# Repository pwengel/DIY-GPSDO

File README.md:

# DIY-GPSDO

Bearbeitet von Lukas

Paste the contents (2 files) of the symbols folder into [for me, this is Dokumente]/KiCad/8.0/symbols/
Symbols for the Pico: https://github.com/ncarandini/KiCad-RP-Pico

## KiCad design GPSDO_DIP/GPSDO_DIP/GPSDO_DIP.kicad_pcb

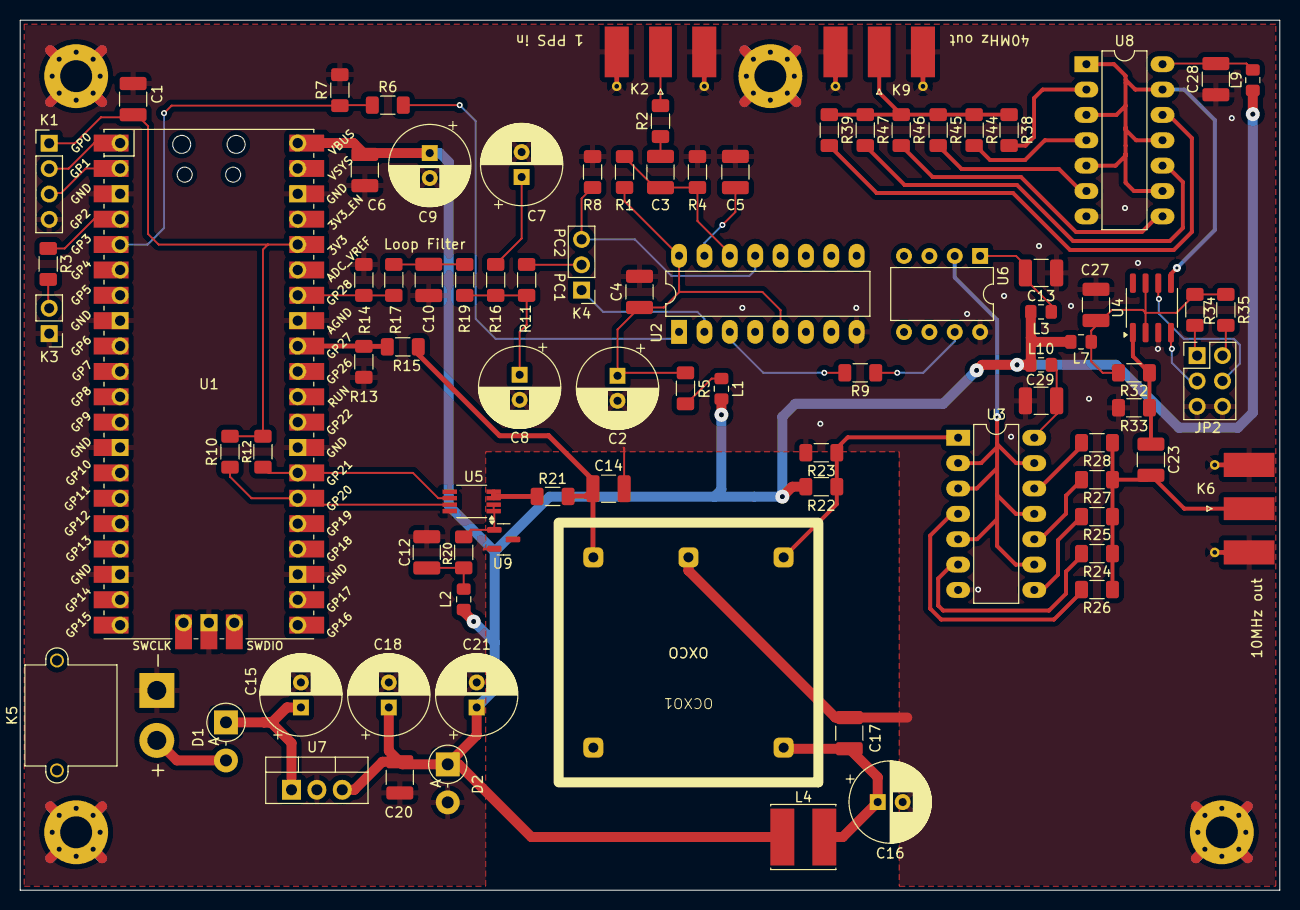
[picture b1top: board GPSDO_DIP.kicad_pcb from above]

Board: 2 copper layers, 126.1 x 87.1 mm, 87 parts (0 on the bottom side), 59 nets.

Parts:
C1, C4, C6, C12, C13, C14, C17, C20, C23, C27, C28, C29: 100n; C_1210_3225Metric_Pad1.33x2.70mm_HandSolder
C2, C7, C16, C21: 47µ; CP_Radial_D8.0mm_P2.50mm
C3, C10: 1µ; C_1210_3225Metric_Pad1.33x2.70mm_HandSolder
C5: 2.2n; C_1210_3225Metric_Pad1.33x2.70mm_HandSolder
C8: 22µ; CP_Radial_D8.0mm_P2.50mm
C9: 220µ; CP_Radial_D8.0mm_P2.50mm
C15, C18: 470µ; CP_Radial_D8.0mm_P2.50mm
D1: SS24; D_DO-15_P3.81mm_Vertical_AnodeUp
D2: D; D_DO-15_P3.81mm_Vertical_AnodeUp
JP2: Conn_02x03_Odd_Even; PinHeader_2x03_P2.54mm_Vertical
K1: Conn_01x04; PinHeader_1x04_P2.54mm_Vertical
K2, K6, K9: Conn_Coaxial; SMA_Molex_73251-1153_EdgeMount_Horizontal
K3: Conn_01x02; PinHeader_1x02_P2.54mm_Vertical
K4: Jumper_3_Open; PinHeader_1x03_P2.54mm_Vertical
K5: Conn_01x02; AMASS_XT30PW-M_1x02_P2.50mm_Horizontal
L1, L2: 100µ; L_0805_2012Metric_Pad1.15x1.40mm_HandSolder
L3, L7, L9, L10: 10µ; L_0805_2012Metric_Pad1.15x1.40mm_HandSolder
L4: 10µ; L_Cenker_CKCS6045
OCXO1: OSC5A2B02
R1, R4, R16, R22, R23: 22k; R_1206_3216Metric_Pad1.30x1.75mm_HandSolder
R2, R19, R24, R25, R26, R27, R28, R38, R39, R44, R45, R46, R47: 240; R_1206_3216Metric_Pad1.30x1.75mm_HandSolder
R3, R20: 1k; R_1206_3216Metric_Pad1.30x1.75mm_HandSolder
R5: 22; R_1206_3216Metric_Pad1.30x1.75mm_HandSolder
R6, R15, R17: 27k; R_1206_3216Metric_Pad1.30x1.75mm_HandSolder
R7, R13, R14: 47k; R_1206_3216Metric_Pad1.30x1.75mm_HandSolder
R8: 1M; R_1206_3216Metric_Pad1.30x1.75mm_HandSolder
R9, R21: 680; R_1206_3216Metric_Pad1.30x1.75mm_HandSolder
R10, R12: 10k; R_1206_3216Metric_Pad1.30x1.75mm_HandSolder
R11: 160k; R_1206_3216Metric_Pad1.30x1.75mm_HandSolder
R32, R33: 100k; R_1206_3216Metric_Pad1.30x1.75mm_HandSolder
R34, R35: 4.7k; R_1206_3216Metric_Pad1.30x1.75mm_HandSolder
U1: Pico; RPi_Pico_SMD_TH
U2: DIP-16_W7.62mm_LongPads
U3, U8: 74HC14; DIP-14_W7.62mm_LongPads
U4: U1; SOIC-8_3.9x4.9mm_P1.27mm
U5: DAC8571IDGK; VSSOP-8_3.0x3.0mm_P0.65mm
U6: PIC12F675-xP; DIP-8_W7.62mm
U7: LM7805_TO220; TO-220-3_Vertical
U9: LM4040DBZ-4.1; SOT-23

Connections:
/VCC: C6.1, C7.1, C18.1, C20.1, C21.1, D2.1 (K), L1.2, L2.2, L3.1, L4.1, L7.2, L9.1, L10.1, R22.1, U1.40 (VBUS), U7.3 (VO)
/V_LPF: C10.2, R17.2, R19.1
/V_OCXO: C14.1, OCXO1.3 (Vcont), R15.2, R21.1
GND: C1.2, C2.2, C4.2, C5.1, C6.2, C7.2, C8.2, C9.2, C10.1, C12.2, C13.1, C14.2, C15.2, C16.2, C17.2, C18.2, C20.2, C21.2, C27.2, C28.1, C29.1, D2.2 (A), JP2.5, JP2.6, K1.4, K2.2 (Ext), K3.1, K5.1, K6.2 (Ext), K9.2 (Ext), OCXO1.2 (GND), R4.2, R7.2, R8.2, R13.2, R14.2, R23.2, R33.2, U1.3 (GND), U1.8 (GND), U1.13 (GND), U1.18 (GND), U1.23 (GND), U1.28 (GND), U1.33 (AGND), U1.38 (GND), U1.42 (GND), U2.8 (GND), U3.7 (GND), U4.3 (GND), U5.5 (A0), U5.8 (GND), U6.8 (VSS), U7.2 (GND), U8.7 (GND), U9.2 (A)
unnamed: C3.1, R2.1
unnamed: C8.1, R11.2, R16.1, R19.2
unnamed: C9.1, R16.2
unnamed: C12.1, L2.1, R20.1
unnamed: D1.2 (A), K5.2
unnamed: C15.1, D1.1 (K), U7.1 (VI)
unnamed: JP2.1, R34.1
unnamed: JP2.2, R35.2
unnamed: JP2.3, U4.4 (S1)
unnamed: JP2.4, U4.6 (S0)
unnamed: C1.1, K1.1, R10.2, R12.2, U1.36 (3V3)
unnamed: K1.2, U1.1 (GPIO0)
unnamed: K1.3, U1.2 (GPIO1)
unnamed: K2.1 (In), R2.2
unnamed: K3.2, R3.2
unnamed: K4.1 (A), U2.2 (PC1_out)
unnamed: K4.3 (B), R8.1, U2.13 (PC2_out)
unnamed: K4.2 (C), R11.1
unnamed: C23.2, K6.1 (In), R24.1, R25.1, R26.1, R27.1, R28.1
unnamed: K9.1 (In), R38.1, R39.1, R44.1, R45.1, R46.1, R47.1
unnamed: L1.1, R5.1
unnamed: OCXO1.1 (10MHz), R22.2, R23.1, U3.1
unnamed: C16.1, C17.1, L4.2, OCXO1.5 (VCC)
unnamed: R24.2, U3.6
unnamed: R25.2, U3.8
unnamed: R26.2, U3.4
unnamed: R27.2, U3.10
unnamed: R28.2, U3.12
unnamed: R38.2, U8.2
unnamed: R39.2, U8.12
unnamed: R44.2, U8.4
unnamed: R45.2, U8.6
unnamed: R46.2, U8.8
unnamed: R47.2, U8.10
unnamed: R3.1, U1.4 (GPIO2)
unnamed: R6.1, R7.1, U1.5 (GPIO3)
unnamed: R10.1, U1.26 (GPIO20), U5.7 (SDA)
unnamed: R12.1, U1.27 (GPIO21), U5.6 (SCL)
unnamed: R13.1, R15.1, U1.32 (GPIO27_ADC1)
unnamed: R14.1, R17.1, U1.34 (GPIO28_ADC2)
unnamed: R9.2, U2.3 (COMP_in)
unnamed: C5.2, U2.15 (C_LD)
unnamed: C2.1, C4.1, R1.1, R5.2, U2.5 (INH), U2.16 (VCC)
unnamed: R6.2, U2.1 (LD)
unnamed: C3.2, R1.2, R4.1, U2.14 (SIG_in)
unnamed: C29.2, L10.2, U3.14 (VCC)
unnamed: U4.5 (CLK), U8.1, U8.3, U8.5, U8.9, U8.11, U8.13
unnamed: C27.1, L7.1, R32.1, R34.2, R35.1, U4.2 (VDD), U4.7 (OE)
unnamed: C23.1, R32.2, R33.1, U4.1 (X1/CLK)
unnamed: R20.2, U5.1 (V_{DD}), U5.2 (V_{REF}), U9.1 (K)
unnamed: R21.2, U5.3 (V_{SENSE}), U5.4 (V_{OUT})
unnamed: R9.1, U6.7 (GP0)
unnamed: U3.2, U3.3, U3.5, U3.9, U3.11, U3.13, U6.2 (GP5)
unnamed: C13.2, L3.2, U6.1 (VDD)
unnamed: C28.2, L9.2, U8.14 (VCC)

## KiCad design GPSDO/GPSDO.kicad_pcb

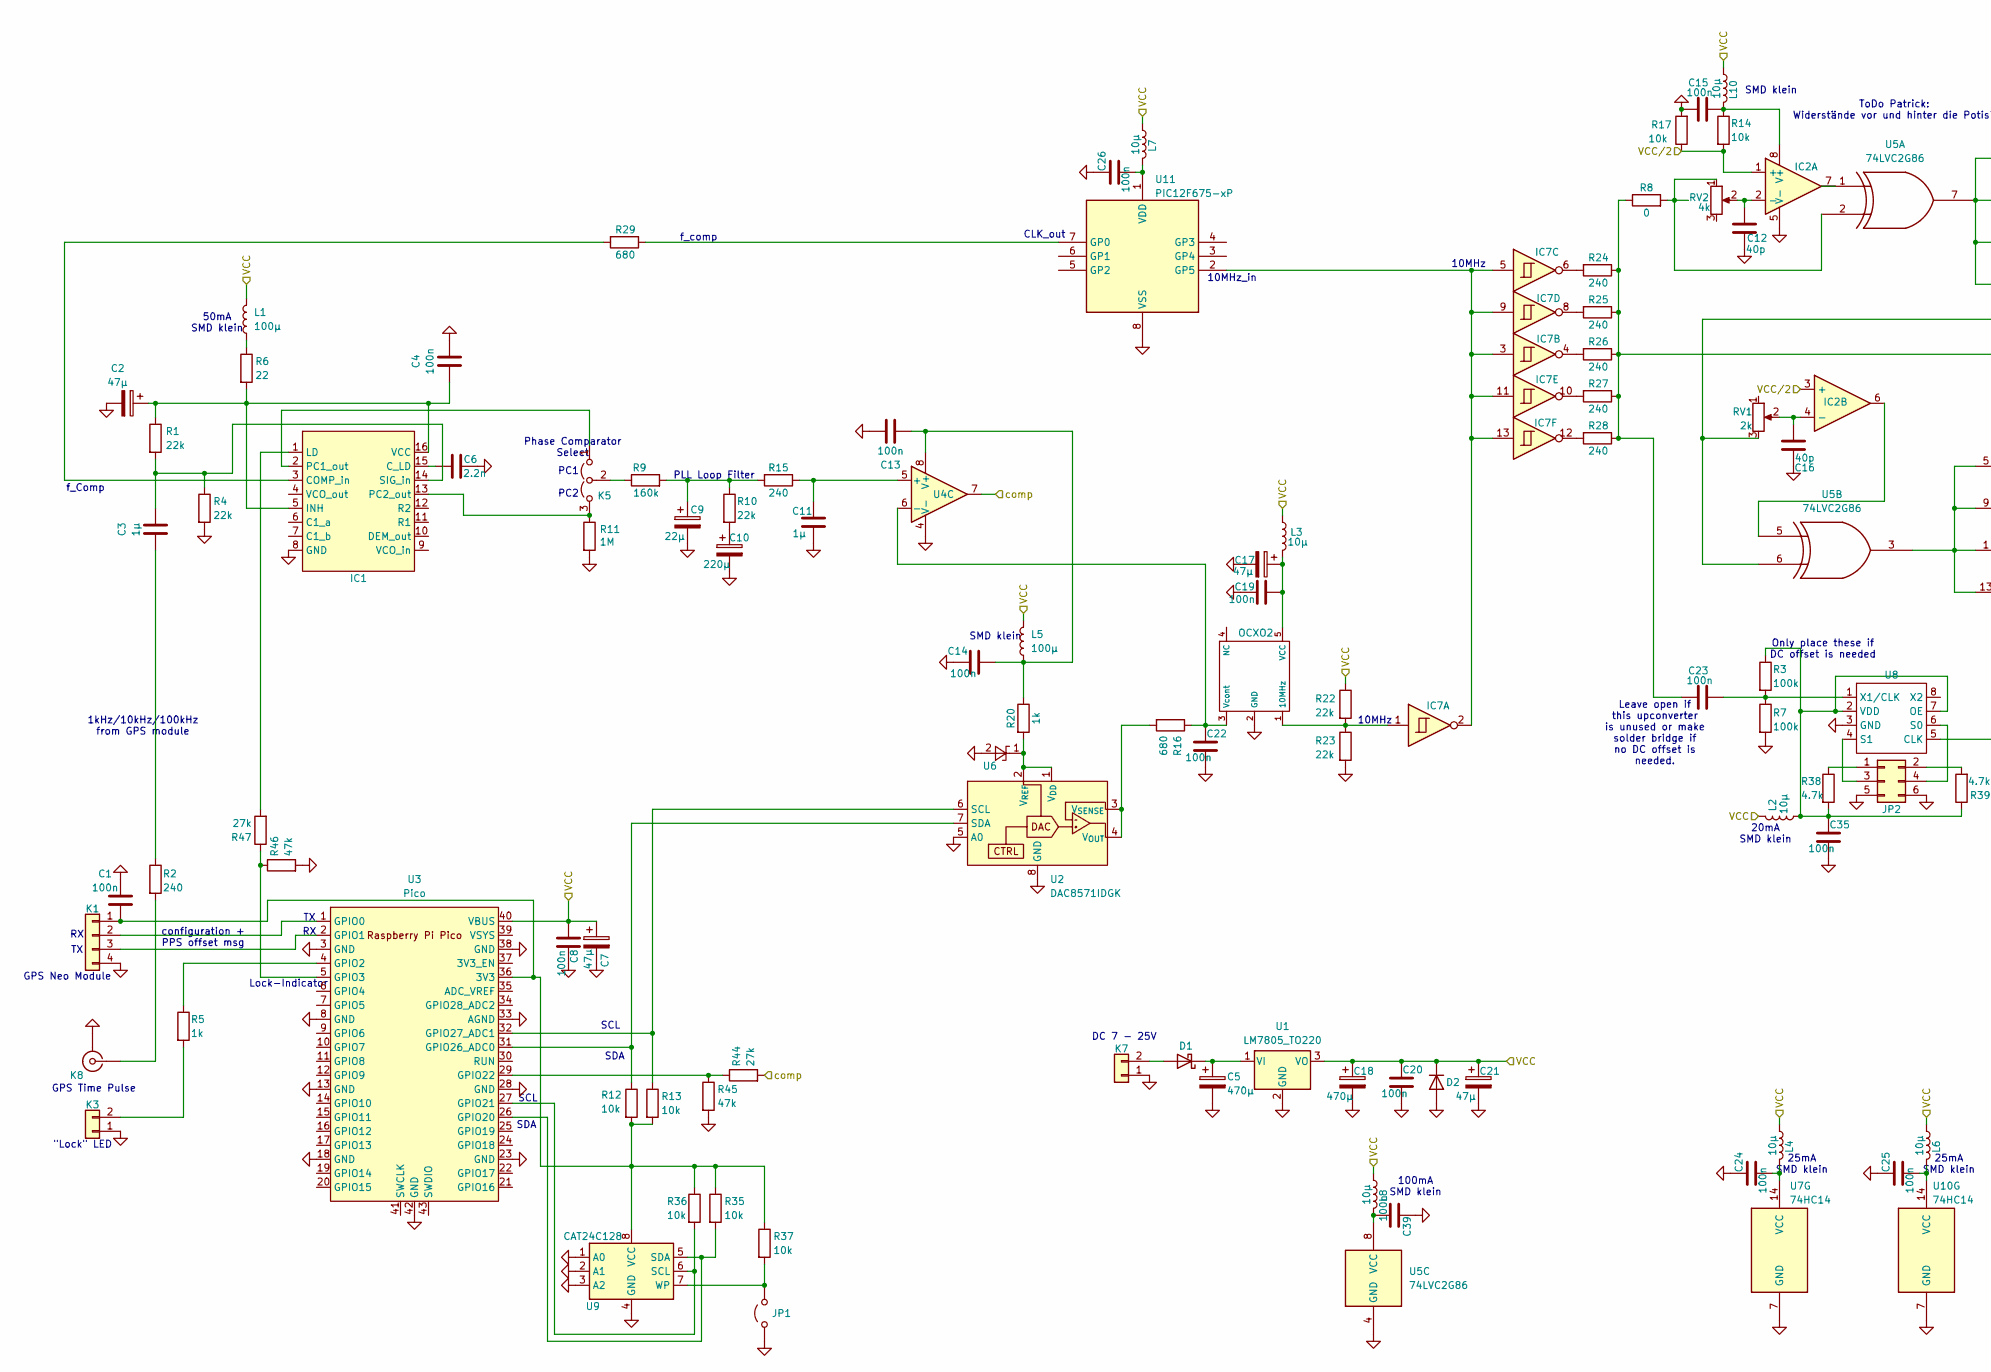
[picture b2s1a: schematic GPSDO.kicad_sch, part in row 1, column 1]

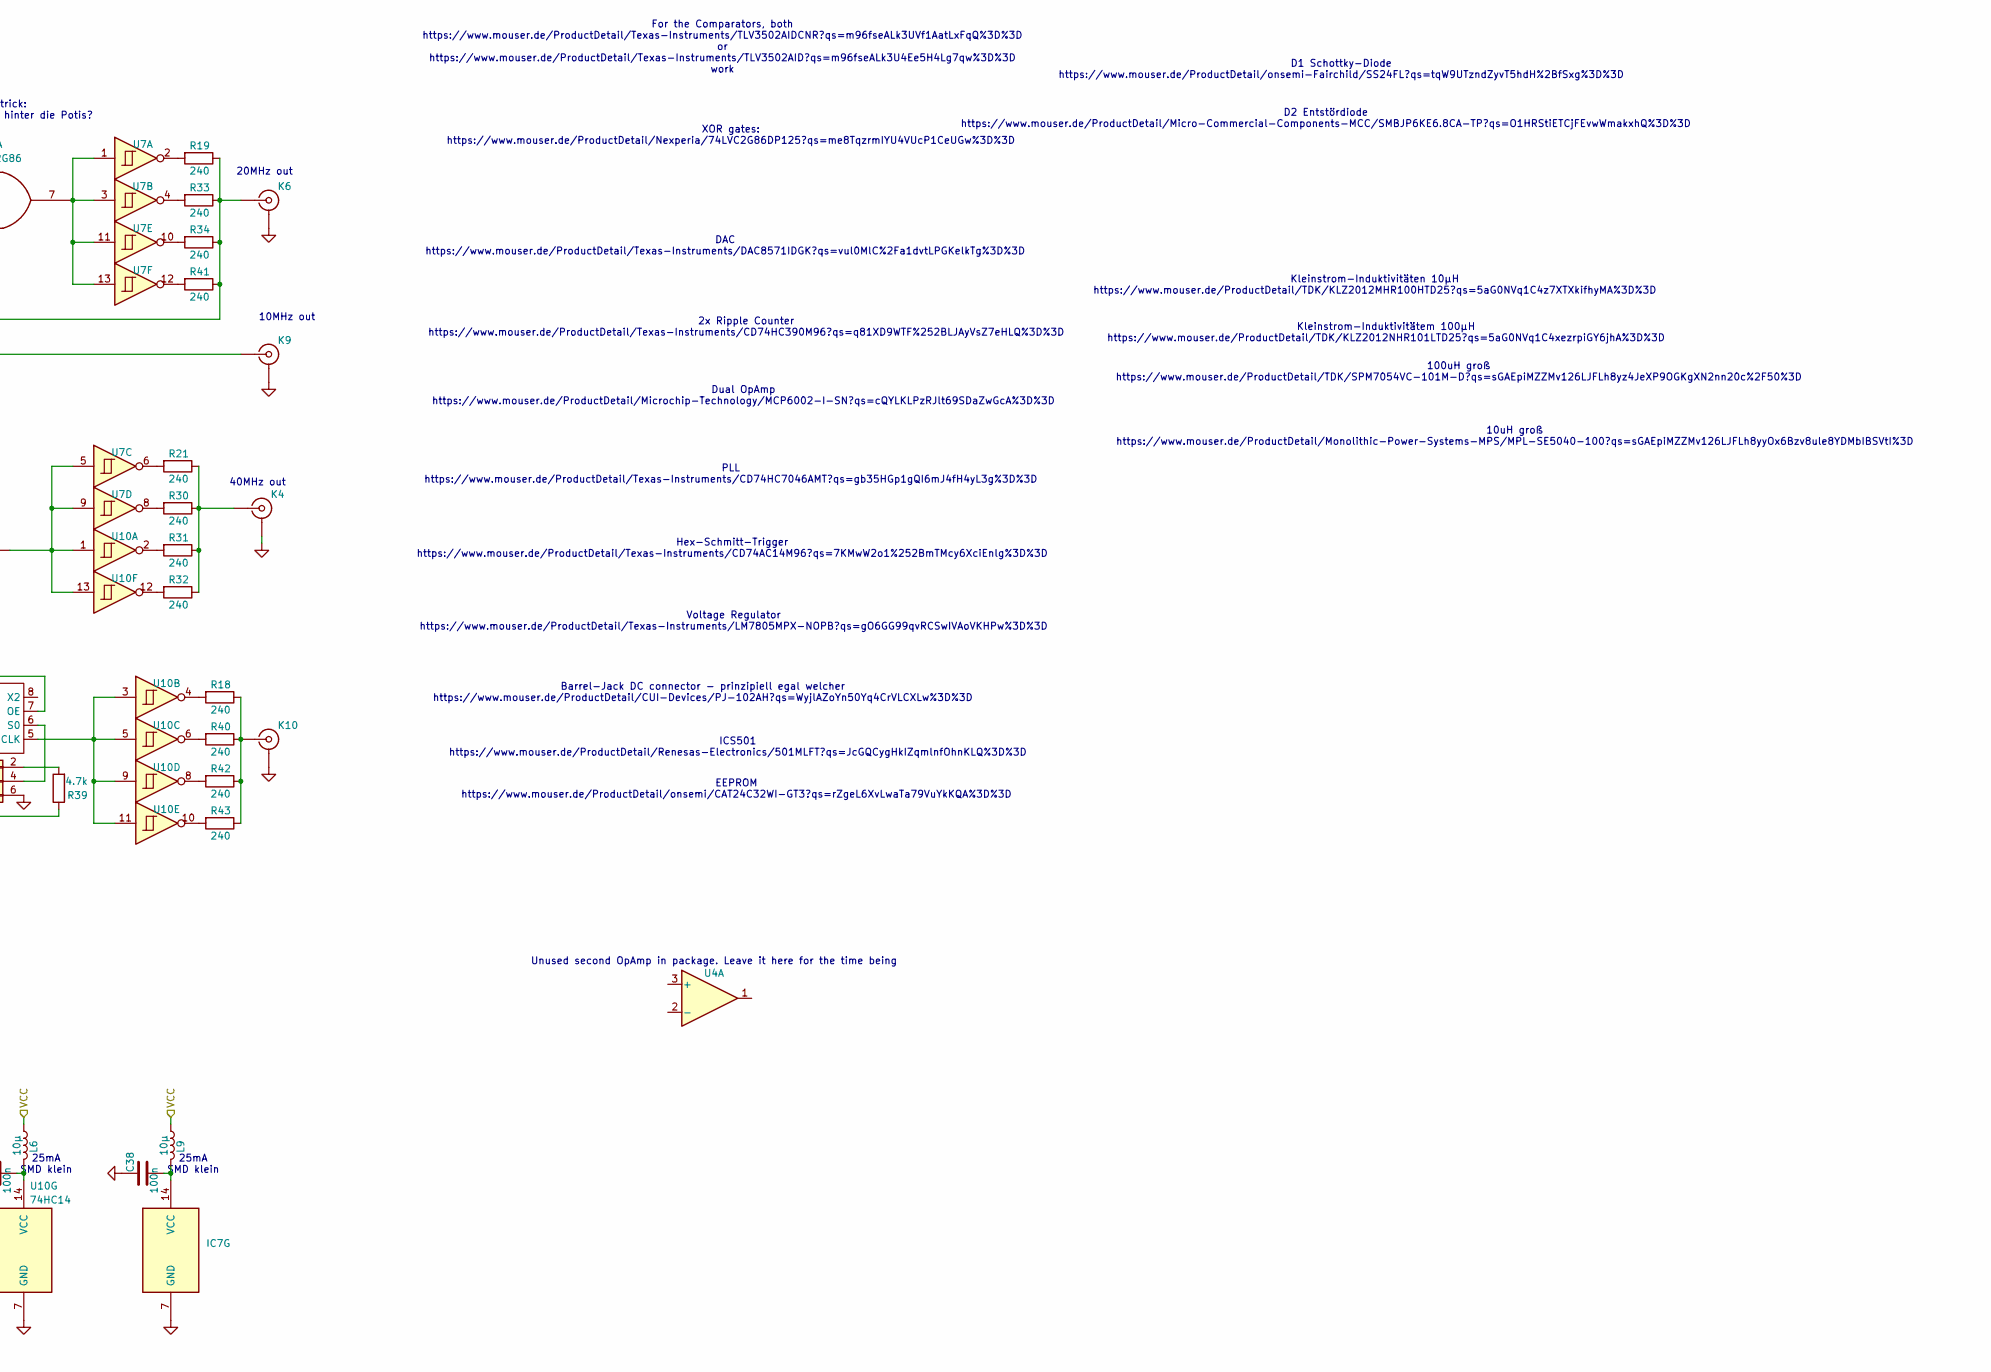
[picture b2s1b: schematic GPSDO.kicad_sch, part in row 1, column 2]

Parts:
C1, C4, C8, C13, C14, C15, C19, C20, C22, C23, C24, C25, C26, C35, C38, C39: 100n; C_1210_3225Metric_Pad1.33x2.70mm_HandSolder
C2, C7, C17, C21: 47µ; CP_Elec_4x5.3
C3, C11: 1µ; C_Rect_L7.2mm_W5.5mm_P5.00mm_FKS2_FKP2_MKS2_MKP2
C5, C18: 470µ; CP_Elec_6.3x9.9
C6: 2.2n; C_1210_3225Metric_Pad1.33x2.70mm_HandSolder
C9: 22µ; CP_EIA-7343-43_Kemet-X_Pad2.25x2.55mm_HandSolder
C10: 220µ; CP_EIA-7343-43_Kemet-X_Pad2.25x2.55mm_HandSolder
C12, C16: 40p; C_1210_3225Metric_Pad1.33x2.70mm_HandSolder
D1: SS24; D_SOD-123F
D2: D; D_SMB
IC1: SOIC-16_3.9x9.9mm_P1.27mm
IC2: SOT-23-8_Handsoldering
IC7: 74HC14; SOIC-14_3.9x8.7mm_P1.27mm
JP1: Jumper_2_Open; PinHeader_1x02_P2.54mm_Vertical
JP2: Conn_02x03_Odd_Even; PinHeader_2x03_P2.54mm_Vertical
K1: Conn_01x04; PinHeader_1x04_P2.54mm_Vertical
K3: Conn_01x02; PinHeader_1x02_P2.54mm_Vertical
K4, K6, K8, K9, K10: Conn_Coaxial; SMA_Molex_73251-1153_EdgeMount_Horizontal
K5: Jumper_3_Open; PinHeader_1x03_P2.54mm_Vertical
K7: Conn_01x02; AMASS_XT30PW-M_1x02_P2.50mm_Horizontal
L1, L5: 100µ; L_0805_2012Metric_Pad1.15x1.40mm_HandSolder
L2, L4, L6, L7, L8, L9, L10: 10µ; L_0805_2012Metric_Pad1.15x1.40mm_HandSolder
L3: 10µ; L_Cenker_CKCS6045
OCXO2: OSC5A2B02
R1, R4, R10, R22, R23: 22k; R_0805_2012Metric_Pad1.20x1.40mm_HandSolder
R2, R15, R18, R19, R21, R24, R25, R26, R27, R28, R30, R31, R32, R33, R34, R40, R41, R42, R43: 240; R_0805_2012Metric_Pad1.20x1.40mm_HandSolder
R3, R7: 100k; R_0805_2012Metric_Pad1.20x1.40mm_HandSolder
R5, R20: 1k; R_0805_2012Metric_Pad1.20x1.40mm_HandSolder
R6: 22; R_0805_2012Metric_Pad1.20x1.40mm_HandSolder
R8: 0; R_0805_2012Metric_Pad1.20x1.40mm_HandSolder
R9: 160k; R_0805_2012Metric_Pad1.20x1.40mm_HandSolder
R11: 1M; R_0805_2012Metric_Pad1.20x1.40mm_HandSolder
R12, R13, R14, R17, R35, R36, R37: 10k; R_0805_2012Metric_Pad1.20x1.40mm_HandSolder
R16, R29: 680; R_0805_2012Metric_Pad1.20x1.40mm_HandSolder
R38, R39: 4.7k; R_0805_2012Metric_Pad1.20x1.40mm_HandSolder
R44, R47: 27k; R_0805_2012Metric_Pad1.20x1.40mm_HandSolder
R45, R46: 47k; R_0805_2012Metric_Pad1.20x1.40mm_HandSolder
RV1: 2k; Potentiometer_Bourns_3314S_Horizontal
RV2: 4k; Potentiometer_Bourns_3314J_Vertical
U1: LM7805_TO220; SOT-223-3_TabPin2
U2: DAC8571IDGK; VSSOP-8_3.0x3.0mm_P0.65mm
U3: Pico; RPi_Pico_SMD_TH
U4: AD8620; SOIC-8_3.9x4.9mm_P1.27mm
U5: 74LVC2G86; TSSOP-8_3x3mm_P0.65mm
U6: LM4040DBZ-4.1; SOT-23
U7, U10: 74HC14; SOIC-14_3.9x8.7mm_P1.27mm
U8: U1; SOIC-8_3.9x4.9mm_P1.27mm
U9: CAT24C128; SOIC-8_3.9x4.9mm_P1.27mm
U11: PIC12F675-xP; DIP-8_W7.62mm

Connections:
/VCC: C7.1, C8.1, C18.1, C20.1, C21.1, D2.1 (K), L1.2, L2.2, L3.1, L4.1, L5.2, L6.1, L7.1, L8.1, L9.1, L10.1, R22.1, U1.3 (VO), U3.40 (VBUS)
/VCC/2: IC2.1 (+), IC2.3 (+), R14.2, R17.1
/comp: R44.2, U4.7
GND: C1.2, C2.2, C4.2, C5.2, C6.1, C7.2, C8.2, C9.2, C10.2, C11.1, C12.1, C13.2, C14.2, C15.2, C16.1, C17.2, C18.2, C19.2, C20.2, C21.2, C22.2, C24.1, C25.1, C26.1, C35.2, C38.1, C39.1, D2.2 (A), IC1.8 (GND), IC2.5 (V-), IC7.7 (GND), JP1.1 (A), JP2.5, JP2.6, K1.4, K3.1, K4.2 (Ext), K6.2 (Ext), K7.1, K8.2 (Ext), K9.2 (Ext), K10.2 (Ext), OCXO2.2 (GND), R4.2, R7.2, R11.2, R17.2, R23.2, R45.2, R46.2, U1.2 (GND), U2.5 (A0), U2.8 (GND), U3.3 (GND), U3.8 (GND), U3.13 (GND), U3.18 (GND), U3.23 (GND), U3.28 (GND), U3.33 (AGND), U3.38 (GND), U3.42 (GND), U4.4 (V-), U5.4 (GND), U6.2 (A), U7.7 (GND), U8.3 (GND), U9.1 (A0), U9.2 (A1), U9.3 (A2), U9.4 (GND), U10.7 (GND), U11.8 (VSS)
unnamed: C3.1, R2.1
unnamed: C9.1, R9.2, R10.1, R15.2
unnamed: C10.1, R10.2
unnamed: D1.2 (A), K7.2
unnamed: C5.1, D1.1 (K), U1.1 (VI)
unnamed: IC1.3 (COMP_in), R29.2
unnamed: C6.2, IC1.15 (C_LD)
unnamed: C2.1, C4.1, IC1.5 (INH), IC1.16 (VCC), R1.1, R6.2
unnamed: IC1.1 (LD), R47.2
unnamed: IC1.2 (PC1_out), K5.1 (A)
unnamed: IC1.13 (PC2_out), K5.3 (B), R11.1
unnamed: C3.2, IC1.14 (SIG_in), R1.2, R4.1
unnamed: IC2.6, U5.5
unnamed: IC2.7, U5.1
unnamed: C12.2, IC2.2 (-), RV2.2
unnamed: C15.1, IC2.8 (V+), L10.2, R14.1
unnamed: C16.2, IC2.4 (-), RV1.2
unnamed: IC7.4, R26.2
unnamed: IC7.6, R24.2
unnamed: IC7.8, R25.2
unnamed: IC7.10, R27.2
unnamed: IC7.12, R28.2
unnamed: C38.2, IC7.14 (VCC), L9.2
unnamed: JP1.2 (B), R37.2, U9.7 (WP)
unnamed: JP2.1, R38.1
unnamed: JP2.2, R39.2
unnamed: JP2.3, U8.4 (S1)
unnamed: JP2.4, U8.6 (S0)
unnamed: C1.1, K1.1, R12.2, R13.2, R35.1, R36.1, R37.1, U3.36 (3V3), U9.8 (VCC)
unnamed: K1.2, U3.1 (GPIO0)
unnamed: K1.3, U3.2 (GPIO1)
unnamed: K3.2, R5.2
unnamed: K4.1 (In), R21.1, R30.1, R31.1, R32.1
unnamed: K5.2 (C), R9.1
unnamed: K6.1 (In), R19.1, R33.1, R34.1, R41.1, RV1.3, U5.6
unnamed: K8.1 (In), R2.2
unnamed: C23.2, K9.1 (In), R8.1, R24.1, R25.1, R26.1, R27.1, R28.1
unnamed: K10.1 (In), R18.1, R40.1, R42.1, R43.1
unnamed: L1.1, R6.1
unnamed: IC7.1, OCXO2.1 (10MHz), R22.2, R23.1
unnamed: C17.1, C19.1, L3.2, OCXO2.5 (VCC)
unnamed: C22.1, OCXO2.3 (Vcont), R16.1, U4.6 (-)
unnamed: R8.2, RV2.1, U5.2
unnamed: R18.2, U10.4
unnamed: R19.2, U7.2
unnamed: R21.2, U7.6
unnamed: R30.2, U7.8
unnamed: R31.2, U10.2
unnamed: R32.2, U10.12
unnamed: R33.2, U7.4
unnamed: R34.2, U7.10
unnamed: R40.2, U10.6
unnamed: R41.2, U7.12
unnamed: R42.2, U10.8
unnamed: R43.2, U10.10
unnamed: R13.1, U2.6 (SCL), U3.32 (GPIO27_ADC1)
unnamed: R12.1, U2.7 (SDA), U3.31 (GPIO26_ADC0)
unnamed: R20.2, U2.1 (V_{DD}), U2.2 (V_{REF}), U6.1 (K)
unnamed: R16.2, U2.3 (V_{SENSE}), U2.4 (V_{OUT})
unnamed: R5.1, U3.4 (GPIO2)
unnamed: R46.1, R47.1, U3.5 (GPIO3)
unnamed: R35.2, U3.26 (GPIO20), U9.5 (SDA)
unnamed: R36.2, U3.27 (GPIO21), U9.6 (SCL)
unnamed: R44.1, R45.1, U3.29 (GPIO22)
unnamed: C11.2, R15.1, U4.5 (+)
unnamed: C13.1, C14.1, L5.1, R20.1, U4.8 (V+)
unnamed: U5.7, U7.1, U7.3, U7.11, U7.13
unnamed: C39.2, L8.2, U5.8 (VCC)
unnamed: C24.2, L4.2, U7.14 (VCC)
unnamed: U8.5 (CLK), U10.3, U10.5, U10.9, U10.11
unnamed: C35.1, L2.1, R3.1, R38.2, R39.1, U8.2 (VDD), U8.7 (OE)
unnamed: C23.1, R3.2, R7.1, U8.1 (X1/CLK)
unnamed: U5.3, U7.5, U7.9, U10.1, U10.13
unnamed: C25.2, L6.2, U10.14 (VCC)
unnamed: R29.1, U11.7 (GP0)
unnamed: IC7.2, IC7.3, IC7.5, IC7.9, IC7.11, IC7.13, U11.2 (GP5)
unnamed: C26.2, L7.2, U11.1 (VDD)

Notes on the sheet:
ToDo Patrick: Widerstände vor und hinter die Potis?
XOR gates: https://www.mouser.de/ProductDetail/Nexperia/74LVC2G86DP125?qs=me8TqzrmIYU4VUcP1CeUGw%3D%3D
Kleinstrom-Induktivitätem 100µH https://www.mouser.de/ProductDetail/TDK/KLZ2012NHR101LTD25?qs=5aG0NVq1C4xezrpiGY6jhA%3D%3D
GPS Time Pulse
ICS501 https://www.mouser.de/ProductDetail/Renesas-Electronics/501MLFT?qs=JcGQCygHkIZqmlnfOhnKLQ%3D%3D
PLL https://www.mouser.de/ProductDetail/Texas-Instruments/CD74HC7046AMT?qs=gb35HGp1gQI6mJ4fH4yL3g%3D%3D
Hex-Schmitt-Trigger https://www.mouser.de/ProductDetail/Texas-Instruments/CD74AC14M96?qs=7KMwW2o1%252BmTMcy6XciEnlg%3D%3D
configuration + PPS offset msg
25mA SMD klein
SMD klein
40MHz out
"Lock" LED
50mA SMD klein
10MHz
Dual OpAmp https://www.mouser.de/ProductDetail/Microchip-Technology/MCP6002-I-SN?qs=cQYLKLPzRJlt69SDaZwGcA%3D%3D
2x Ripple Counter https://www.mouser.de/ProductDetail/Texas-Instruments/CD74HC390M96?qs=q81XD9WTF%252BLJAyVsZ7eHLQ%3D%3D
f_comp
10uH groß https://www.mouser.de/ProductDetail/Monolithic-Power-Systems-MPS/MPL-SE5040-100?qs=sGAEpiMZZMv126LJFLh8yyOx6Bzv8ule8YDMbIBSVtI%3D
SDA
10MHz out
100uH groß https://www.mouser.de/ProductDetail/TDK/SPM7054VC-101M-D?qs=sGAEpiMZZMv126LJFLh8yz4JeXP9OGKgXN2nn20c%2F50%3D
D2 Entstördiode https://www.mouser.de/ProductDetail/Micro-Commercial-Components-MCC/SMBJP6KE6.8CA-TP?qs=O1HRStiETCjFEvwWmakxhQ%3D%3D
Voltage Regulator https://www.mouser.de/ProductDetail/Texas-Instruments/LM7805MPX-NOPB?qs=gO6GG99qvRCSwIVAoVKHPw%3D%3D
f_Comp
Lock-Indicator
Leave open if this upconverter is unused or make solder bridge if no DC offset is needed.
CLK_out
EEPROM https://www.mouser.de/ProductDetail/onsemi/CAT24C32WI-GT3?qs=rZgeL6XvLwaTa79VuYkKQA%3D%3D
PLL Loop Filter
GPS Neo Module
Barrel-Jack DC connector - prinzipiell egal welcher https://www.mouser.de/ProductDetail/CUI-Devices/PJ-102AH?qs=WyjlAZoYn50Yq4CrVLCXLw%3D%3D
DC 7 - 25V
Only place these if DC offset is needed
DAC https://www.mouser.de/ProductDetail/Texas-Instruments/DAC8571IDGK?qs=vul0MlC%2Fa1dvtLPGKelkTg%3D%3D
20mA SMD klein
100mA SMD klein
SCL
Phase Comparator Select
Unused second OpAmp in package. Leave it here for the time being
PC1 PC2

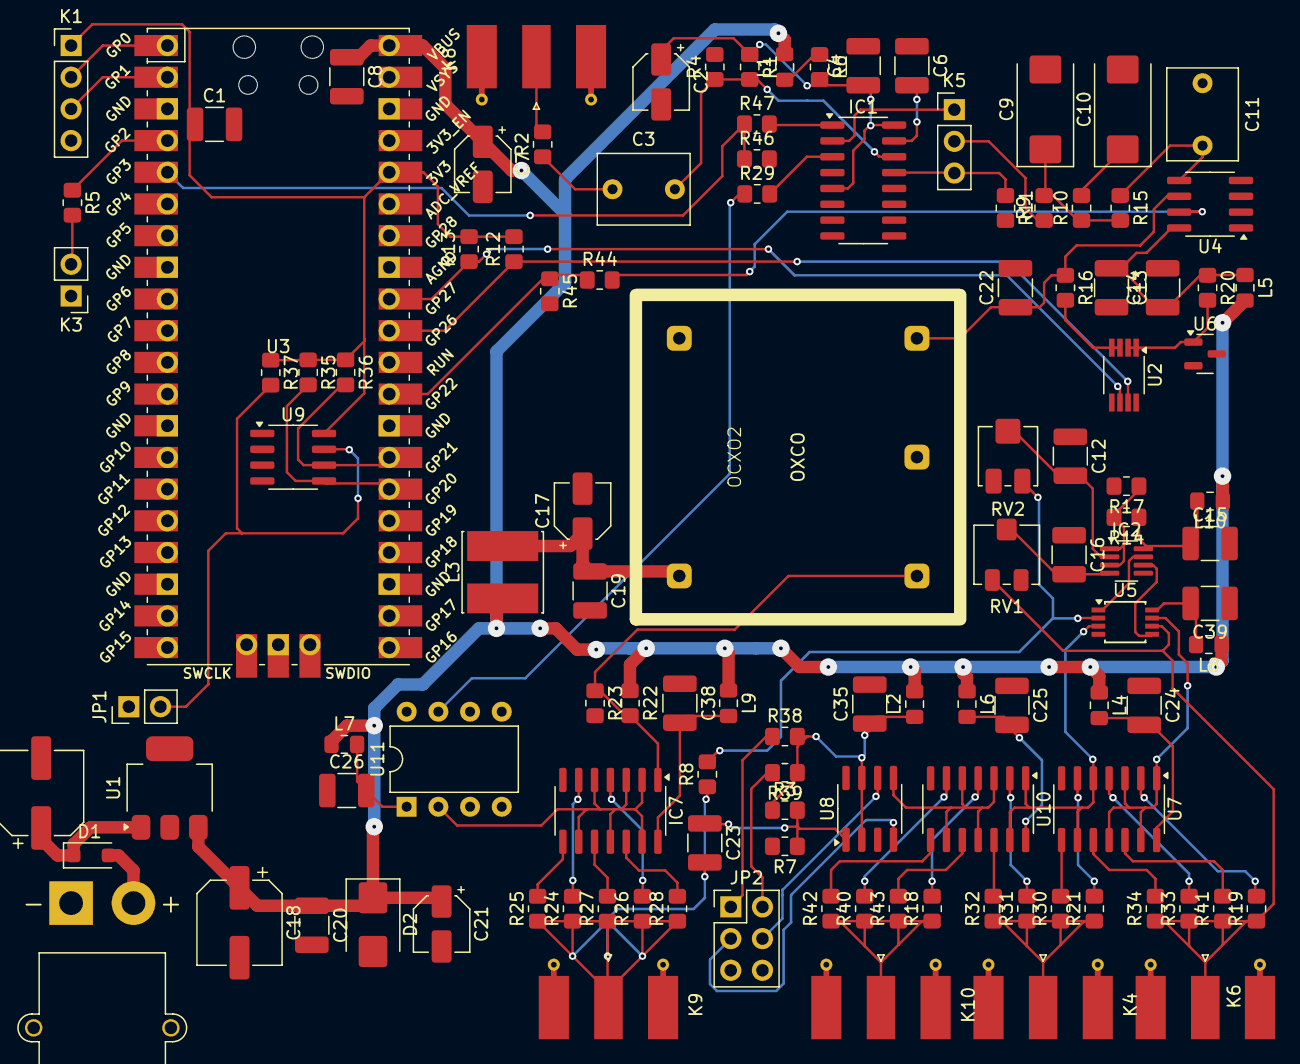
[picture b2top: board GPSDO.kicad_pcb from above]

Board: 2 copper layers, 116 parts (0 on the bottom side), 81 nets.

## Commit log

2024-04-12 added KiCad Project
2024-04-12 Update README.md
    Hallo, das ist ein Test
2024-04-14 changed schematic, OCXO symbol from Gibbi
2024-04-19 Add Frequency Multiplier and Pico
2024-04-22 minor schematic changes, added most footprints
2024-04-22 added LTSpice files for the digital frequency quadrupler
2024-04-22 added footprints and Mouser Links to components
2024-04-24 Started Layout (WIP), minor schematic changes (3.3V supply to GPS neo module, removed voltage divider, since RPico Pins already provide 3.3V only)
2024-05-04 Changed VCC network, added ICS501 frequency multiplier
2024-05-09 added voltage reference to DAC
2024-05-09 buffers added + cleanup
2024-05-12 Layout almost done (GND plane & edge cuts missing), replaced counters with PIC 12F675 MCU for more flexible down conversion and less ICs on the PCB
2024-05-15 VCC net width fix, added voltage dividers for Pico inputs
2024-06-26 Added GPSDO prototype schematic with DIP ICs
2024-07-01 added mounting holes & 10MHz SMA-port, cleaned up labels a bit
2024-10-10 MicroPython Project
    Add a MicroPython Project to programme the Raspbarry Pico which is used for digital processing inside the DIY-GPSDO.
